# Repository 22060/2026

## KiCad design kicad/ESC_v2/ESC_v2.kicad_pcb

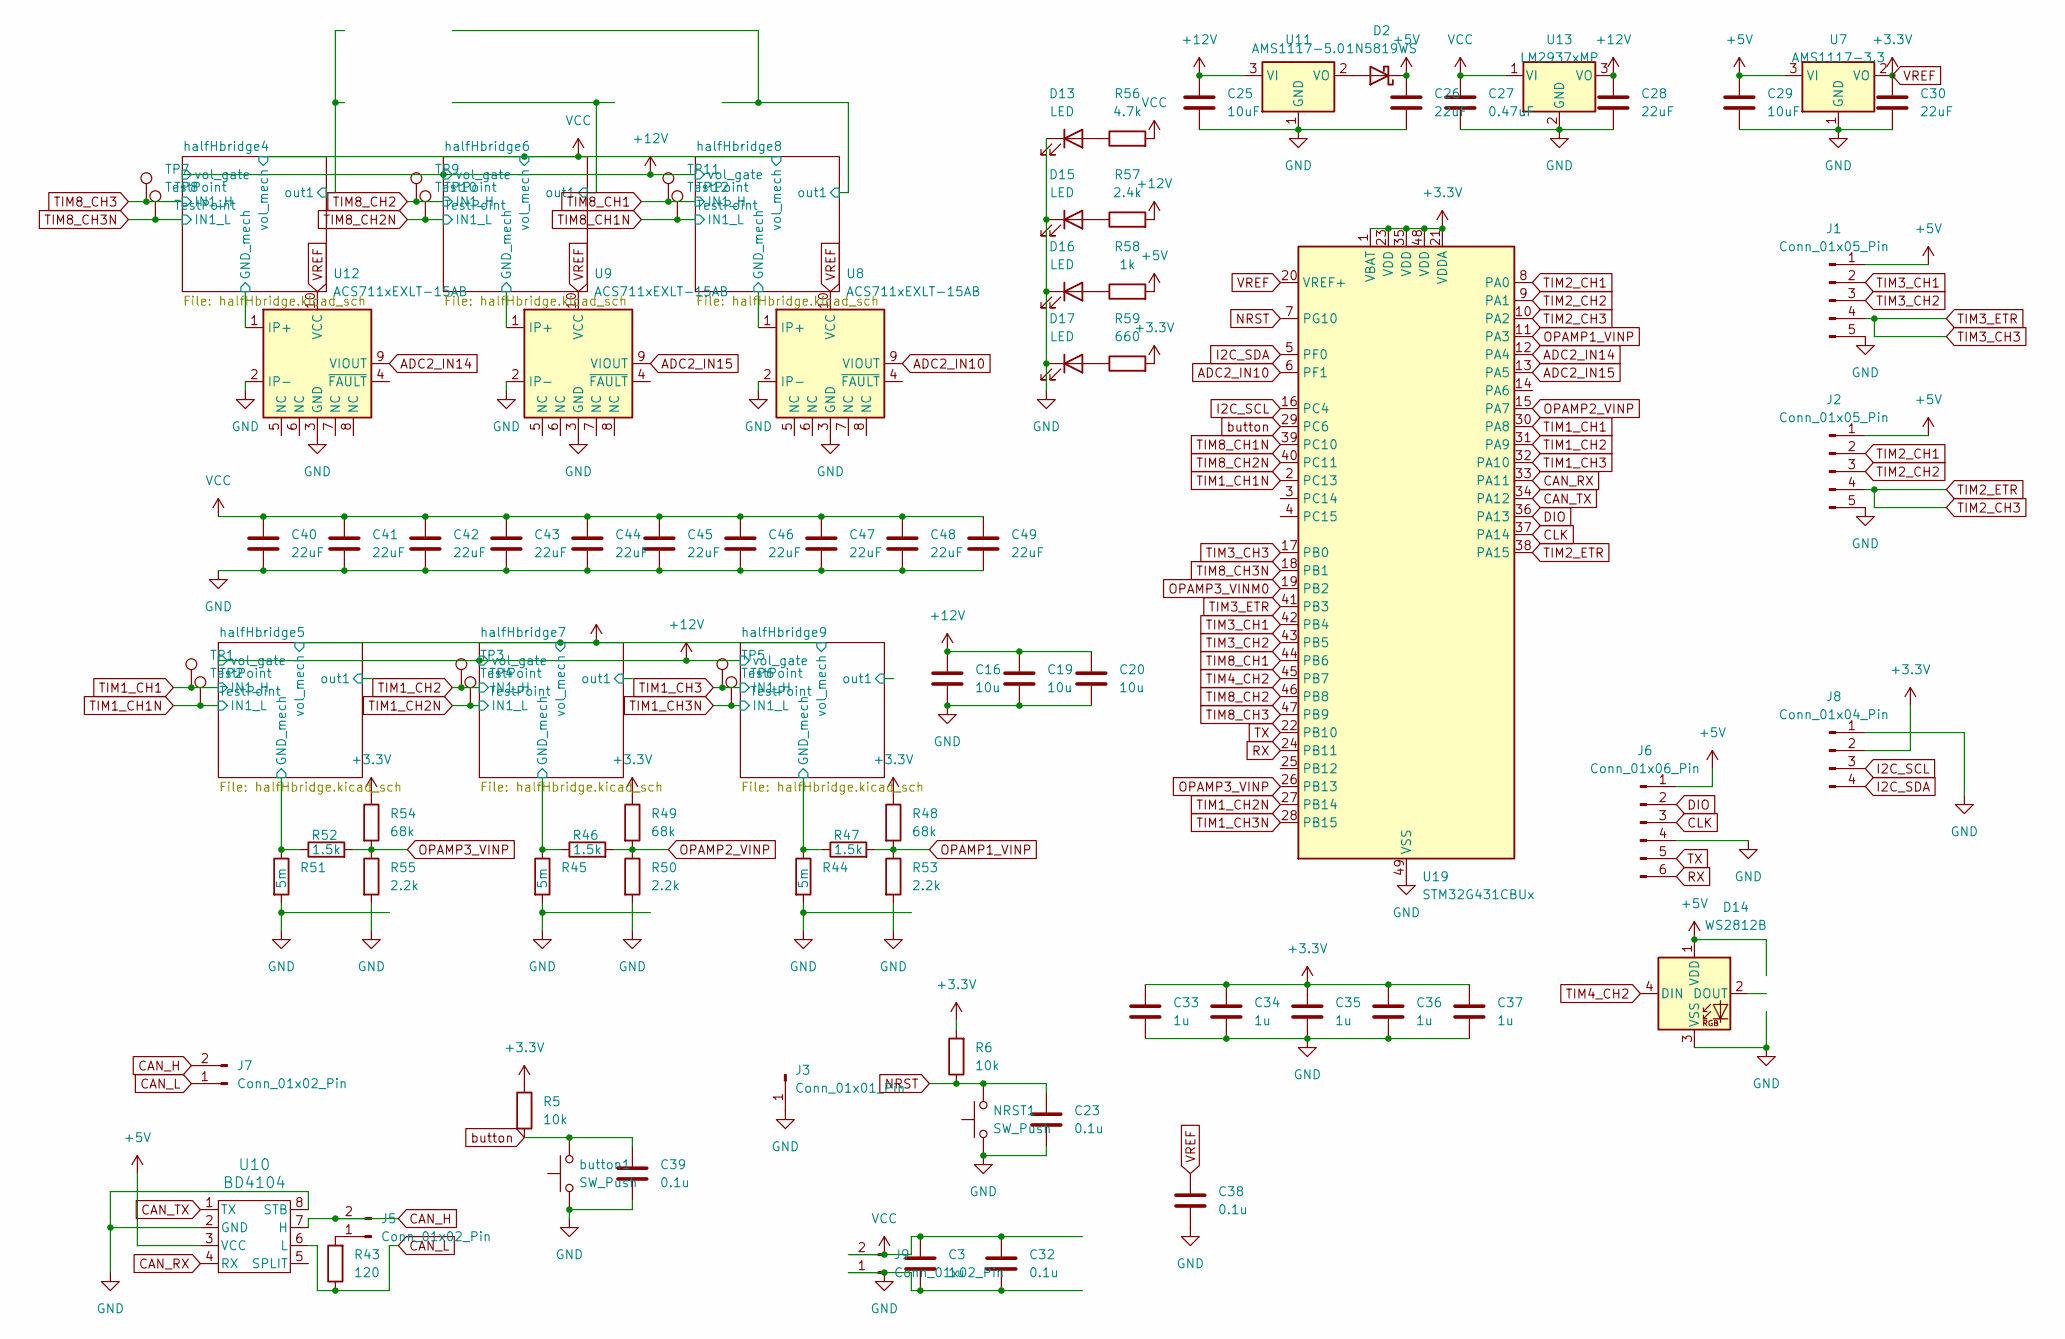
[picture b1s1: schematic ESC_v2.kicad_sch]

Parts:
C3, C33, C34, C35, C36, C37: 1u; C_0402_1005Metric; LCSC C52923
C16, C19, C20: 10u; C_1206_3216Metric; LCSC C13585
C23, C32, C38, C39: 0.1u; C_0402_1005Metric; LCSC C52923
C25, C29: 10uF; C_1206_3216Metric; LCSC C13585
C26, C30: 22uF; C_0805_2012Metric; LCSC C45783
C27: 0.47uF; C_0805_2012Metric_Pad1.18x1.45mm_HandSolder; LCSC C13967
C28, C40, C41, C42, C43, C44, C45, C46, C47, C48, C49: 22uF; C_0603_1608Metric; LCSC C59461
D2: 1N5819WS; D_SOD-323
D13, D15, D16, D17: LED; LED_0603_1608Metric; LCSC C2290
D14: WS2812B; LED_WS2812B_PLCC4_5.0x5.0mm_P3.2mm; LCSC C2761795
J1, J2: Conn_01x05_Pin; JST_XH_S5B-XH-A_1x05_P2.50mm_Horizontal
J3: Conn_01x01_Pin; PinHeader_1x01_P1.00mm_Vertical
J5: Conn_01x02_Pin; PinHeader_1x02_P2.54mm_Vertical
J6: Conn_01x06_Pin; JST_ZH_B6B-ZR_1x06_P1.50mm_Vertical
J7: Conn_01x02_Pin; JST_XH_S2B-XH-A_1x02_P2.50mm_Horizontal
J8: Conn_01x04_Pin; PinSocket_1x04_P2.54mm_Vertical
J9: Conn_01x02_Pin; AMASS_XT30PW-M_1x02_P2.50mm_Horizontal
NRST1: SW_Push; Aitendo_SW SMD 6x3.5
R5, R6: 10k; R_0402_1005Metric_Pad0.72x0.64mm_HandSolder; LCSC C25744
R43: 120; R_0402_1005Metric_Pad0.72x0.64mm_HandSolder; LCSC C25079
R44, R45, R51: 5m; R_2010_5025Metric_Pad1.40x2.65mm_HandSolder; LCSC C912931
R46, R47, R52: 1.5k; R_0402_1005Metric_Pad0.72x0.64mm_HandSolder; LCSC C25867
R48, R49, R54: 68k; R_0402_1005Metric_Pad0.72x0.64mm_HandSolder; LCSC C25768
R50, R53, R55: 2.2k; R_0402_1005Metric_Pad0.72x0.64mm_HandSolder; LCSC C25879
R56: 4.7k; R_0402_1005Metric_Pad0.72x0.64mm_HandSolder; LCSC C25900
R57: 2.4k; R_0402_1005Metric_Pad0.72x0.64mm_HandSolder; LCSC C25879
R58: 1k; R_0402_1005Metric_Pad0.72x0.64mm_HandSolder; LCSC C11702
R59: 660; R_0402_1005Metric_Pad0.72x0.64mm_HandSolder; LCSC C25177
TP1, TP2, TP3, TP4, TP5, TP6, TP7, TP8, TP9, TP10, TP11, TP12: TestPoint; TestPoint_Pad_D1.0mm
U7: AMS1117-3.3; SOT-223-3_TabPin2; LCSC C6186
U8, U9, U12: ACS711xEXLT-15AB; Allegro_QFN-12-10-1EP_3x3mm_P0.5mm; LCSC C146412
U10: BD4104; SOP-J8; LCSC C2937651
U11: AMS1117-5.0; SOT-223-3_TabPin2; LCSC C6187
U13: LM2937xMP; SOT-223-3_TabPin2; LCSC C127023
U19: STM32G431CBUx; QFN-48-1EP_7x7mm_P0.5mm_EP5.6x5.6mm; LCSC C529356
button1: SW_Push; Aitendo_SW SMD 6x3.5

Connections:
+5V: C26.1, C29.1, D2.1 (K), D14.1 (VDD), J1.1, J2.1, J6.1, R58.2, U7.3 (VI), U10.3 (VCC)
+12V: C16.1, C19.1, C20.1, C25.1, C28.1, R57.2, U11.3 (VI), U13.3 (VO); also elsewhere on the board
/halfHbridge4/GND_mech: U12.1 (IP+); also elsewhere on the board
/halfHbridge5/GND_mech: R51.1, R52.1; also elsewhere on the board
/halfHbridge6/GND_mech: U9.1 (IP+); also elsewhere on the board
/halfHbridge7/GND_mech: R45.1, R46.1; also elsewhere on the board
/halfHbridge8/GND_mech: U8.1 (IP+); also elsewhere on the board
/halfHbridge9/GND_mech: R44.1, R47.1; also elsewhere on the board
ADC2_IN10: U8.9 (VIOUT), U19.6 (PF1)
ADC2_IN14: U12.9 (VIOUT), U19.12 (PA4)
ADC2_IN15: U9.9 (VIOUT), U19.13 (PA5)
CAN_H: J5.2, J7.2, U10.7 (H)
CAN_L: J7.1, R43.1, U10.6 (L)
CAN_RX: U10.4 (RX), U19.33 (PA11)
CAN_TX: U10.1 (TX), U19.34 (PA12)
CLK: J6.3, U19.37 (PA14)
DIO: J6.2, U19.36 (PA13)
GND: C3.2, C16.2, C19.2, C20.2, C23.2, C25.2, C26.2, C27.2, C28.2, C29.2, C30.2, C32.2, C33.2, C34.2, C35.2, C36.2, C37.2, C38.2, C39.2, C40.2, C41.2, C42.2, C43.2, C44.2, C45.2, C46.2, C47.2, C48.2, C49.2, D13.1 (K), D14.3 (VSS), D15.1 (K), D16.1 (K), D17.1 (K), J1.5, J2.5, J3.1, J6.4, J8.1, J9.1, NRST1.1, R44.2, R45.2, R50.2, R51.2, R53.2, R55.2, U7.1 (GND), U8.2 (IP-), U8.3 (GND), U9.2 (IP-), U9.3 (GND), U10.2 (GND), U10.8 (STB), U11.1 (GND), U12.2 (IP-), U12.3 (GND), U13.2 (GND), U19.49 (VSS), button1.1; also elsewhere on the board
I2C_SCL: J8.3, U19.16 (PC4)
I2C_SDA: J8.4, U19.5 (PF0)
NRST: C23.1, NRST1.2, R6.1, U19.7 (PG10)
unnamed: D2.2 (A), U11.2 (VO)
unnamed: D13.2 (A), R56.1
unnamed: D15.2 (A), R57.1
unnamed: D16.2 (A), R58.1
unnamed: D17.2 (A), R59.1
unnamed: J5.1, R43.2
OPAMP1_VINP: R47.2, R48.2, R53.1, U19.11 (PA3)
OPAMP2_VINP: R46.2, R49.2, R50.1, U19.15 (PA7)
OPAMP3_VINM0: U19.19 (PB2)
OPAMP3_VINP: R52.2, R54.2, R55.1, U19.26 (PB13)
RX: J6.6, U19.24 (PB11)
TIM1_CH1: TP1.1, U19.30 (PA8); also elsewhere on the board
TIM1_CH1N: TP2.1, U19.2 (PC13); also elsewhere on the board
TIM1_CH2: TP3.1, U19.31 (PA9); also elsewhere on the board
TIM1_CH2N: TP4.1, U19.27 (PB14); also elsewhere on the board
TIM1_CH3: TP5.1, U19.32 (PA10); also elsewhere on the board
TIM1_CH3N: TP6.1, U19.28 (PB15); also elsewhere on the board
TIM2_CH1: J2.2, U19.8 (PA0)
TIM2_CH2: J2.3, U19.9 (PA1)
TIM2_CH3: J2.4, U19.10 (PA2), U19.38 (PA15)
TIM3_CH1: J1.2, U19.42 (PB4)
TIM3_CH2: J1.3, U19.43 (PB5)
TIM3_CH3: J1.4, U19.17 (PB0), U19.41 (PB3)
TIM4_CH2: D14.4 (DIN), U19.45 (PB7)
TIM8_CH1: TP11.1, U19.44 (PB6); also elsewhere on the board
TIM8_CH1N: TP12.1, U19.39 (PC10); also elsewhere on the board
TIM8_CH2: TP9.1, U19.46 (PB8); also elsewhere on the board
TIM8_CH2N: TP10.1, U19.40 (PC11); also elsewhere on the board
TIM8_CH3: TP7.1, U19.47 (PB9); also elsewhere on the board
TIM8_CH3N: TP8.1, U19.18 (PB1); also elsewhere on the board
TX: J6.5, U19.22 (PB10)
VCC: C3.1, C27.1, C32.1, C40.1, C41.1, C42.1, C43.1, C44.1, C45.1, C46.1, C47.1, C48.1, C49.1, J9.2, R56.2, U13.1 (VI); also elsewhere on the board
VREF: C30.1, C33.1, C34.1, C35.1, C36.1, C37.1, C38.1, J8.2, R5.1, R6.2, R48.1, R49.1, R54.1, R59.2, U7.2 (VO), U8.10 (VCC), U9.10 (VCC), U12.10 (VCC), U19.1 (VBAT), U19.20 (VREF+), U19.21 (VDDA), U19.23 (VDD), U19.35 (VDD), U19.48 (VDD)
button: C39.1, R5.2, U19.29 (PC6), button1.2

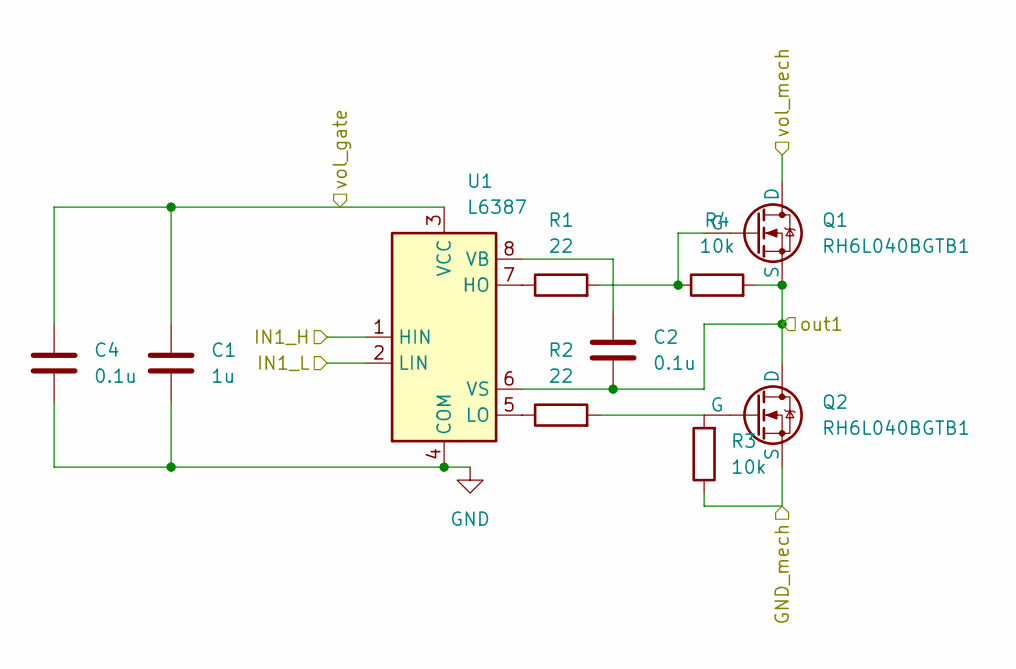
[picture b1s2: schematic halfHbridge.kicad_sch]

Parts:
C1: 1u; C_0402_1005Metric; LCSC C52923
C2: 0.1u; C_0402_1005Metric; LCSC C307331
C4: 0.1u; C_0402_1005Metric; LCSC C52923
Q1, Q2: RH6L040BGTB1; VSONP-8-1EP_5x6_P1.27mm; LCSC C49384064
R1, R2: 22; R_0402_1005Metric_Pad0.72x0.64mm_HandSolder; LCSC C25092
R3, R4: 10k; R_0402_1005Metric_Pad0.72x0.64mm_HandSolder; LCSC C25744
U1: L6387; SOIC-8_3.9x4.9mm_P1.27mm; LCSC C234211

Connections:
+12V: C1.1, C4.1, U1.3 (VCC); also elsewhere on the board
/halfHbridge5/GND_mech: Q2.1 (S), R3.1; also elsewhere on the board
/halfHbridge5/out1: C2.2, Q1.1 (S), Q2.3 (D), R4.2, U1.6 (VS)
GND: C1.2, C4.2, U1.4 (COM); also elsewhere on the board
unnamed: Q1.2 (G), R1.2, R4.1
unnamed: Q2.2 (G), R2.2, R3.2
unnamed: R1.1, U1.7 (HO)
unnamed: R2.1, U1.5 (LO)
unnamed: C2.1, U1.8 (VB)
TIM1_CH1: U1.1 (HIN); also elsewhere on the board
TIM1_CH1N: U1.2 (LIN); also elsewhere on the board
VCC: Q1.3 (D); also elsewhere on the board

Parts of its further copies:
C5, C9, C10, C17, C21: 1u; C_0402_1005Metric; LCSC C52923
C6, C11, C12, C18, C22: 0.1u; C_0402_1005Metric; LCSC C307331
C7, C8, C13, C14, C15: 0.1u; C_0402_1005Metric; LCSC C52923
Q3, Q4, Q5, Q6, Q7, Q8, Q9, Q10, Q11, Q12: RH6L040BGTB1; VSONP-8-1EP_5x6_P1.27mm; LCSC C49384064
R7, R8, R13, R14, R15, R16, R25, R26, R31, R32: 22; R_0402_1005Metric_Pad0.72x0.64mm_HandSolder; LCSC C25092
R9, R10, R17, R18, R19, R20, R27, R28, R33, R34: 10k; R_0402_1005Metric_Pad0.72x0.64mm_HandSolder; LCSC C25744
U2, U3, U4, U5, U6: L6387; SOIC-8_3.9x4.9mm_P1.27mm; LCSC C234211

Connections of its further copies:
+12V: C5.1, C7.1, C8.1, C9.1, C10.1, C13.1, C14.1, C15.1, C17.1, C21.1, U2.3 (VCC), U3.3 (VCC), U4.3 (VCC), U5.3 (VCC), U6.3 (VCC); also elsewhere on the board
/halfHbridge4/GND_mech: Q4.1 (S), R9.1; also elsewhere on the board
/halfHbridge4/out1: C6.2, Q3.1 (S), Q4.3 (D), R10.2, U2.6 (VS)
/halfHbridge6/GND_mech: Q6.1 (S), R18.1; also elsewhere on the board
/halfHbridge6/out1: C12.2, Q5.1 (S), Q6.3 (D), R20.2, U4.6 (VS)
/halfHbridge7/GND_mech: Q8.1 (S), R17.1; also elsewhere on the board
/halfHbridge7/out1: C11.2, Q7.1 (S), Q8.3 (D), R19.2, U3.6 (VS)
/halfHbridge8/GND_mech: Q10.1 (S), R27.1; also elsewhere on the board
/halfHbridge8/out1: C18.2, Q9.1 (S), Q10.3 (D), R28.2, U5.6 (VS)
/halfHbridge9/GND_mech: Q12.1 (S), R33.1; also elsewhere on the board
/halfHbridge9/out1: C22.2, Q11.1 (S), Q12.3 (D), R34.2, U6.6 (VS)
GND: C5.2, C7.2, C8.2, C9.2, C10.2, C13.2, C14.2, C15.2, C17.2, C21.2, U2.4 (COM), U3.4 (COM), U4.4 (COM), U5.4 (COM), U6.4 (COM); also elsewhere on the board
unnamed: Q3.2 (G), R7.2, R10.1
unnamed: Q4.2 (G), R8.2, R9.2
unnamed: Q5.2 (G), R15.2, R20.1
unnamed: Q6.2 (G), R16.2, R18.2
unnamed: Q7.2 (G), R13.2, R19.1
unnamed: Q8.2 (G), R14.2, R17.2
unnamed: Q9.2 (G), R25.2, R28.1
unnamed: Q10.2 (G), R26.2, R27.2
unnamed: Q11.2 (G), R31.2, R34.1
unnamed: Q12.2 (G), R32.2, R33.2
unnamed: R7.1, U2.7 (HO)
unnamed: R8.1, U2.5 (LO)
unnamed: C6.1, U2.8 (VB)
unnamed: R13.1, U3.7 (HO)
unnamed: R14.1, U3.5 (LO)
unnamed: C11.1, U3.8 (VB)
unnamed: R15.1, U4.7 (HO)
unnamed: R16.1, U4.5 (LO)
unnamed: C12.1, U4.8 (VB)
unnamed: R25.1, U5.7 (HO)
unnamed: R26.1, U5.5 (LO)
unnamed: C18.1, U5.8 (VB)
unnamed: R31.1, U6.7 (HO)
unnamed: R32.1, U6.5 (LO)
unnamed: C22.1, U6.8 (VB)
TIM1_CH2: U3.1 (HIN); also elsewhere on the board
TIM1_CH2N: U3.2 (LIN); also elsewhere on the board
TIM1_CH3: U6.1 (HIN); also elsewhere on the board
TIM1_CH3N: U6.2 (LIN); also elsewhere on the board
TIM8_CH1: U5.1 (HIN); also elsewhere on the board
TIM8_CH1N: U5.2 (LIN); also elsewhere on the board
TIM8_CH2: U4.1 (HIN); also elsewhere on the board
TIM8_CH2N: U4.2 (LIN); also elsewhere on the board
TIM8_CH3: U2.1 (HIN); also elsewhere on the board
TIM8_CH3N: U2.2 (LIN); also elsewhere on the board
VCC: Q3.3 (D), Q5.3 (D), Q7.3 (D), Q9.3 (D), Q11.3 (D); also elsewhere on the board

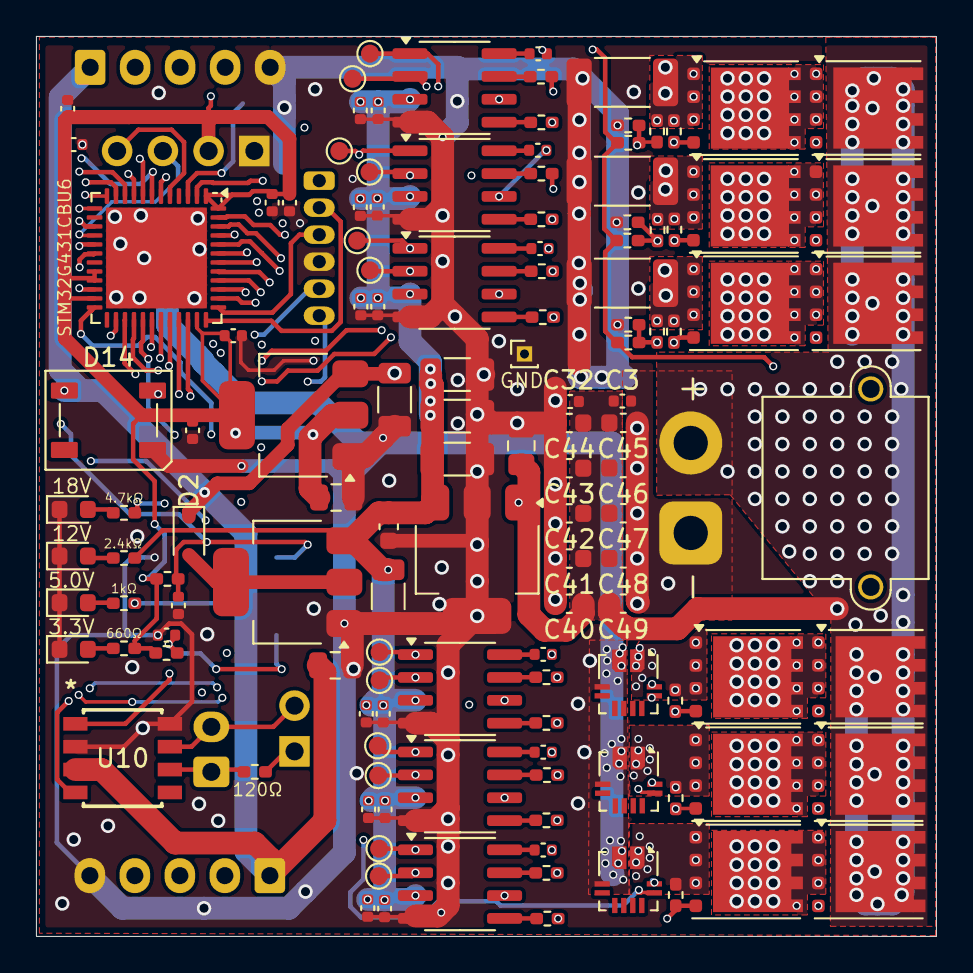
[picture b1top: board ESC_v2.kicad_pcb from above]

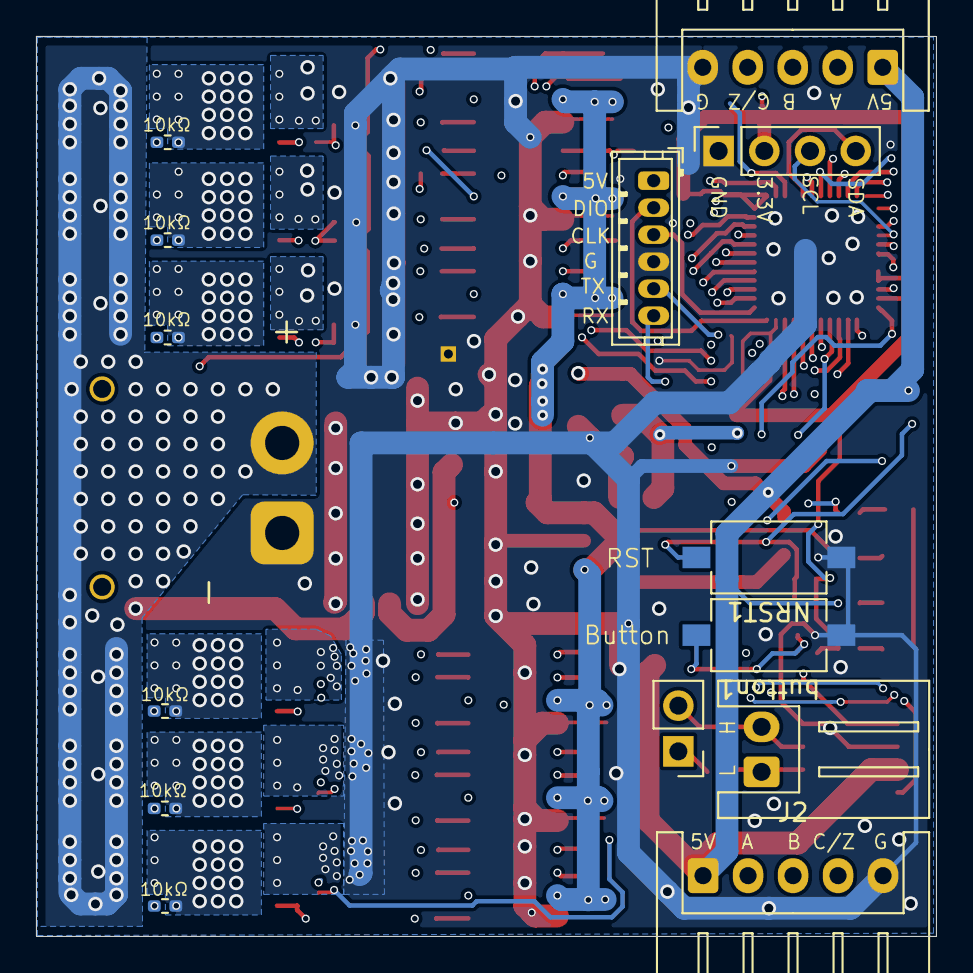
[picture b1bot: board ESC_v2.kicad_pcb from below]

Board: 4 copper layers, 50.0 x 50.0 mm, 144 parts (14 on the bottom side), 90 nets.

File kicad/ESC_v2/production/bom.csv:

Designator,Footprint,Quantity,Value,LCSC Part #
"BUTTON1, NRST1",Aitendo_SW SMD 6x3.5,2,SW_Push,
"C1, C10, C17, C21, C3, C33, C34, C35, C36, C37, C5, C9",402,12,1u,C52923
"C11, C12, C18, C2, C22, C6",402,6,0.1u,C307331
"C13, C14, C15, C23, C32, C38, C39, C4, C7, C8",402,10,0.1u,C52923
"C16, C19, C20",1206,3,10u,C13585
"C25, C29",1206,2,10uF,C13585
"C26, C30",805,2,22uF,C45783
C27,805,1,0.47uF,C13967
"C28, C40, C41, C42, C43, C44, C45, C46, C47, C48, C49",603,11,22uF,C59461
D13,603,1,LED,C2290
D14,LED_WS2812B_PLCC4_5.0x5.0mm_P3.2mm,1,WS2812B,C2761795
"D15, D16, D17",805,3,LED,C2290
D2,D_SOD-323,1,1N5819WS,C191023
"Q1, Q10, Q11, Q12, Q2, Q3, Q4, Q5, Q6, Q7, Q8, Q9",VSONP-8-1EP_5x6_P1.27mm,12,RH6L040BGTB1,C49384064
"R1, R13, R14, R15, R16, R2, R25, R26, R31, R32, R7, R8",402,12,22,C25092
"R10, R17, R18, R19, R20, R27, R28, R3, R33, R34, R4, R5, R6, R9",402,14,10k,C25744
R43,402,1,120,C25079
"R44, R45, R51",2010,3,5m,C912931
"R46, R47, R52",402,3,1.5k,C25867
"R48, R49, R54",402,3,68k,C25768
"R50, R53, R55",402,3,2.2k,C25879
R56,402,1,4.7k,C25900
R57,402,1,2.4k,C25879
R58,402,1,1k,C11702
R59,402,1,660,C25177
"U1, U2, U3, U4, U5, U6",SOIC-8_3.9x4.9mm_P1.27mm,6,L6387,C234211
U10,SOP-J8,1,BD4104,C2937651
U11,SOT-223-3_TabPin2,1,AMS1117-5.0,C6187
"U12, U8, U9",Allegro_QFN-12-10-1EP_3x3mm_P0.5mm,3,ACS711xEXLT-15AB,C146412
U13,SOT-223-3_TabPin2,1,LM2937xMP,C127023
U19,QFN-48-1EP_7x7mm_P0.5mm_EP5.6x5.6mm,1,STM32G431CBUx,C529356
U7,SOT-223-3_TabPin2,1,AMS1117-3.3,C6186

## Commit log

2026-04-06 add report folder
2026-05-16 add ESC_v3 final ver
